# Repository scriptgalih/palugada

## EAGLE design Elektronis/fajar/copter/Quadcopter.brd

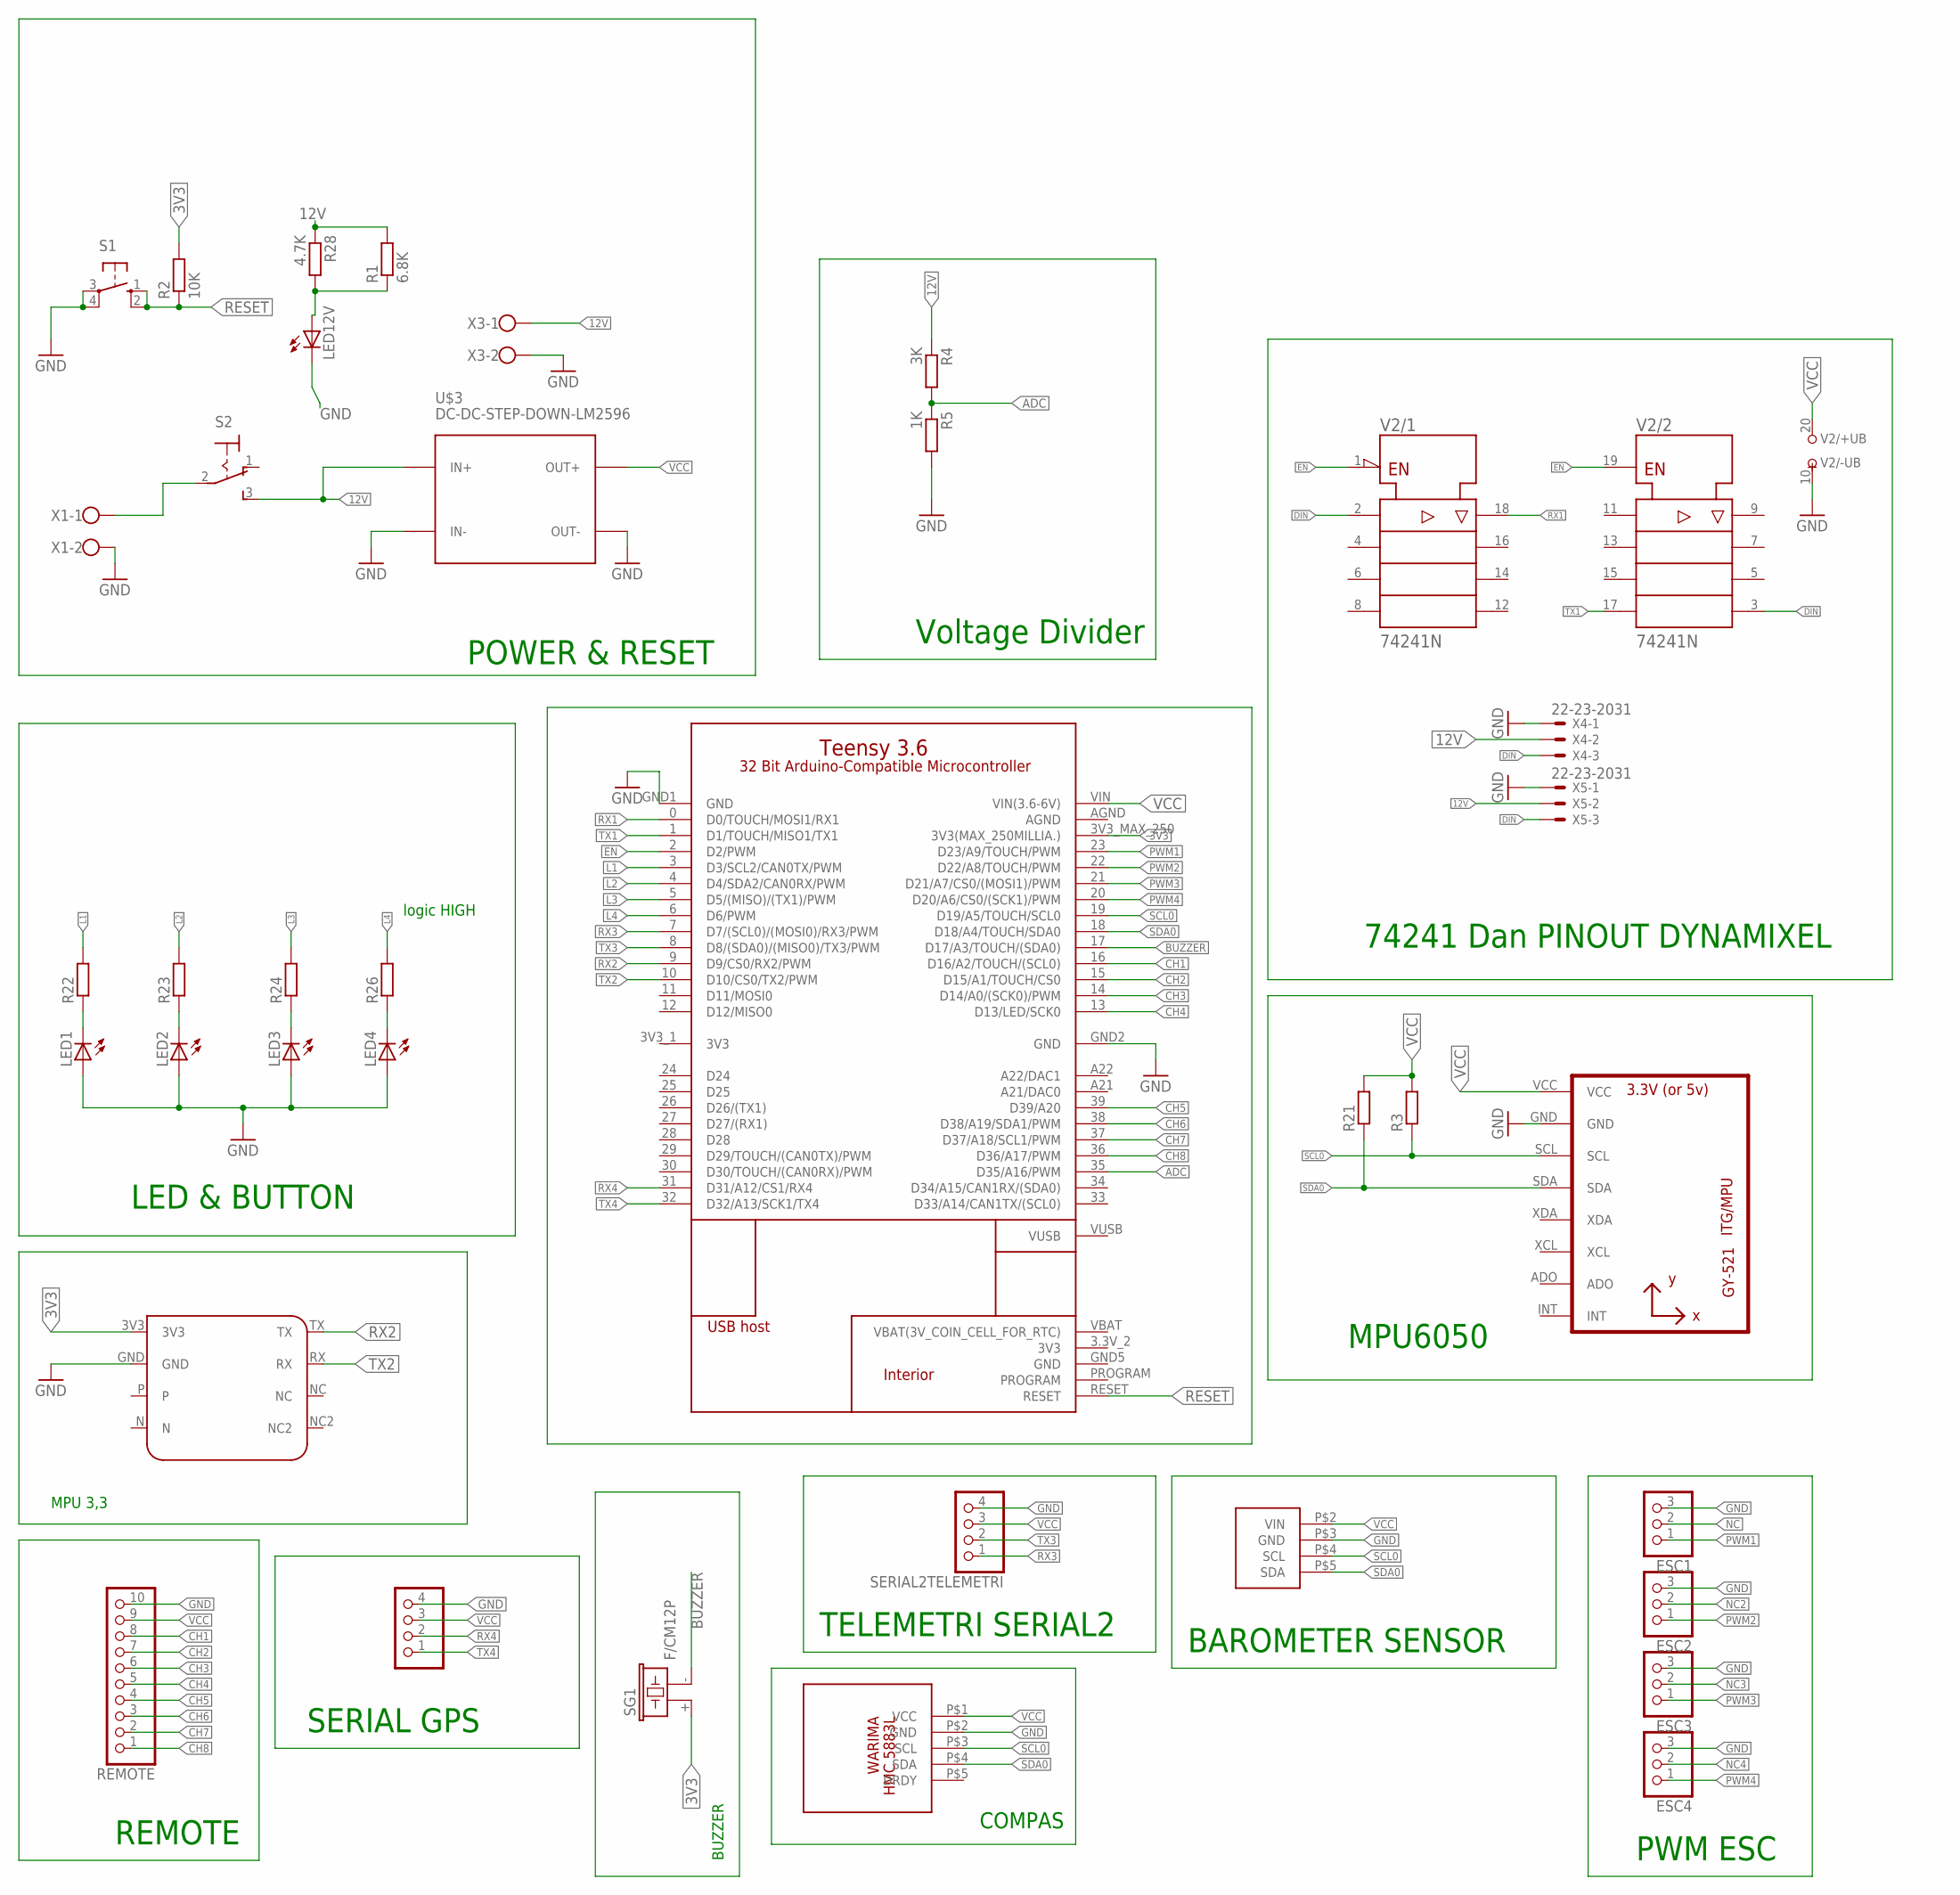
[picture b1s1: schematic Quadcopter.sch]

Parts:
ESC1, ESC2, ESC3, ESC4: PINHD-1X3; 1X03
LED1, LED2, LED3, LED4, LED12V: LED3MM
R1: 6.8K; 0207/10
R2: 10K; 0207/10
R3, R21, R22, R23, R24, R26: R-EU_0207/7; 0207/7
R4: 3K; 0207/10
R5: 1K; 0207/10
R28: 4.7K; 0207/10
REMOTE: PINHD-1X10; 1X10
S1: 10-XX; B3F-10XX
S2: 320-916
SERIAL2TELEMETRI, SERIAL2TELEMETRI1: PINHD-1X4; 1X04
SG1: F/CM12P
U1: GY-521MPU6050; GY-521
U$1: TEENSY-3.6_ONLY_HOLES
U$2: URANUS2
U$3: DC-DC-STEP-DOWN-LM2596
U$4: BMP180
U$5: HMC588L; HMC5883L
V2: 74241N; DIL20
X1, X3: W237-102
X4, X5: 22-23-2031

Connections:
3V3: R2.2, SG1.+ (1), U$1.3V3_1 (3V3), U$1.3V3_MAX_250 (3V3(MAX_250MILLIA.)), U$2.3V3
12V: R1.2, R4.1, R28.1, S2.3 (S), U$3.IN+, X3.1, X4.2, X5.2
ADC: R4.2, R5.1, U$1.35 (D35/A16/PWM)
AGND: U$1.AGND
BUZZER: SG1.- (2), U$1.17 (D17/A3/TOUCH/(SDA0))
CH1: REMOTE.8, U$1.16 (D16/A2/TOUCH/(SCL0))
CH2: REMOTE.7, U$1.15 (D15/A1/TOUCH/CS0)
CH3: REMOTE.6, U$1.14 (D14/A0/(SCK0)/PWM)
CH4: REMOTE.5, U$1.13 (D13/LED/SCK0)
CH5: REMOTE.4, U$1.39 (D39/A20)
CH6: REMOTE.3, U$1.38 (D38/A19/SDA1/PWM)
CH7: REMOTE.2, U$1.37 (D37/A18/SCL1/PWM)
CH8: REMOTE.1, U$1.36 (D36/A17/PWM)
DIN: V2.2 (A1), V2.3 (Y4), X4.3, X5.3
EN: U$1.2 (D2/PWM), V2.1 (!G), V2.19 (G)
GND: ESC1.3, ESC2.3, ESC3.3, ESC4.3, LED1.A, LED2.A, LED3.A, LED4.A, LED12V.K (C), R5.2, REMOTE.10, S1.3, S1.4 (P1), SERIAL2TELEMETRI.4, SERIAL2TELEMETRI1.4, U1.GND, U$1.GND1 (GND), U$1.GND2 (GND), U$2.GND, U$3.IN-, U$3.OUT-, U$4.P$3 (GND), U$5.P$2 (GND), V2.10 (-UB), X1.2, X3.2, X4.1, X5.1
L1: R22.2, U$1.3 (D3/SCL2/CAN0TX/PWM)
L2: R23.2, U$1.4 (D4/SDA2/CAN0RX/PWM)
L3: R24.2, U$1.5 (D5/(MISO)/(TX1)/PWM)
L4: R26.2, U$1.6 (D6/PWM)
unnamed: LED1.K (C), R22.1
unnamed: S2.2, X1.1
unnamed: LED2.K (C), R23.1
unnamed: LED3.K (C), R24.1
unnamed: LED4.K (C), R26.1
unnamed: LED12V.A, R1.1, R28.2
NC: ESC1.2
NC2: ESC2.2
NC3: ESC3.2
NC4: ESC4.2
PWM1: ESC1.1, U$1.23 (D23/A9/TOUCH/PWM)
PWM2: ESC2.1, U$1.22 (D22/A8/TOUCH/PWM)
PWM3: ESC3.1, U$1.21 (D21/A7/CS0/(MOSI1)/PWM)
PWM4: ESC4.1, U$1.20 (D20/A6/CS0/(SCK1)/PWM)
RESET: R2.1, S1.1 (S), S1.2 (S1), U$1.RESET
RX1: U$1.0 (D0/TOUCH/MOSI1/RX1), V2.18 (Y1)
RX2: U$1.9 (D9/CS0/RX2/PWM), U$2.TX
RX3: SERIAL2TELEMETRI.1, U$1.7 (D7/(SCL0)/(MOSI0)/RX3/PWM)
RX4: SERIAL2TELEMETRI1.2, U$1.31 (D31/A12/CS1/RX4)
SCL0: R3.1, U1.SCL, U$1.19 (D19/A5/TOUCH/SCL0), U$4.P$4 (SCL), U$5.P$3 (SCL)
SDA0: R21.1, U1.SDA, U$1.18 (D18/A4/TOUCH/SDA0), U$4.P$5 (SDA), U$5.P$4 (SDA)
TX1: U$1.1 (D1/TOUCH/MISO1/TX1), V2.17 (A4)
TX2: U$1.10 (D10/CS0/TX2/PWM), U$2.RX
TX3: SERIAL2TELEMETRI.2, U$1.8 (D8/(SDA0)/(MISO0)/TX3/PWM)
TX4: SERIAL2TELEMETRI1.1, U$1.32 (D32/A13/SCK1/TX4)
VCC: R3.2, R21.2, REMOTE.9, SERIAL2TELEMETRI.3, SERIAL2TELEMETRI1.3, U1.VCC, U$1.VIN (VIN(3.6-6V)), U$3.OUT+, U$4.P$2 (VIN), U$5.P$1 (VCC), V2.20 (+UB)

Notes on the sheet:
MPU 3,3
74241 Dan PINOUT DYNAMIXEL
MPU6050
BAROMETER SENSOR
LED & BUTTON
TELEMETRI SERIAL2
BUZZER
POWER & RESET
logic HIGH
SERIAL GPS
Voltage Divider
REMOTE
COMPAS
PWM ESC

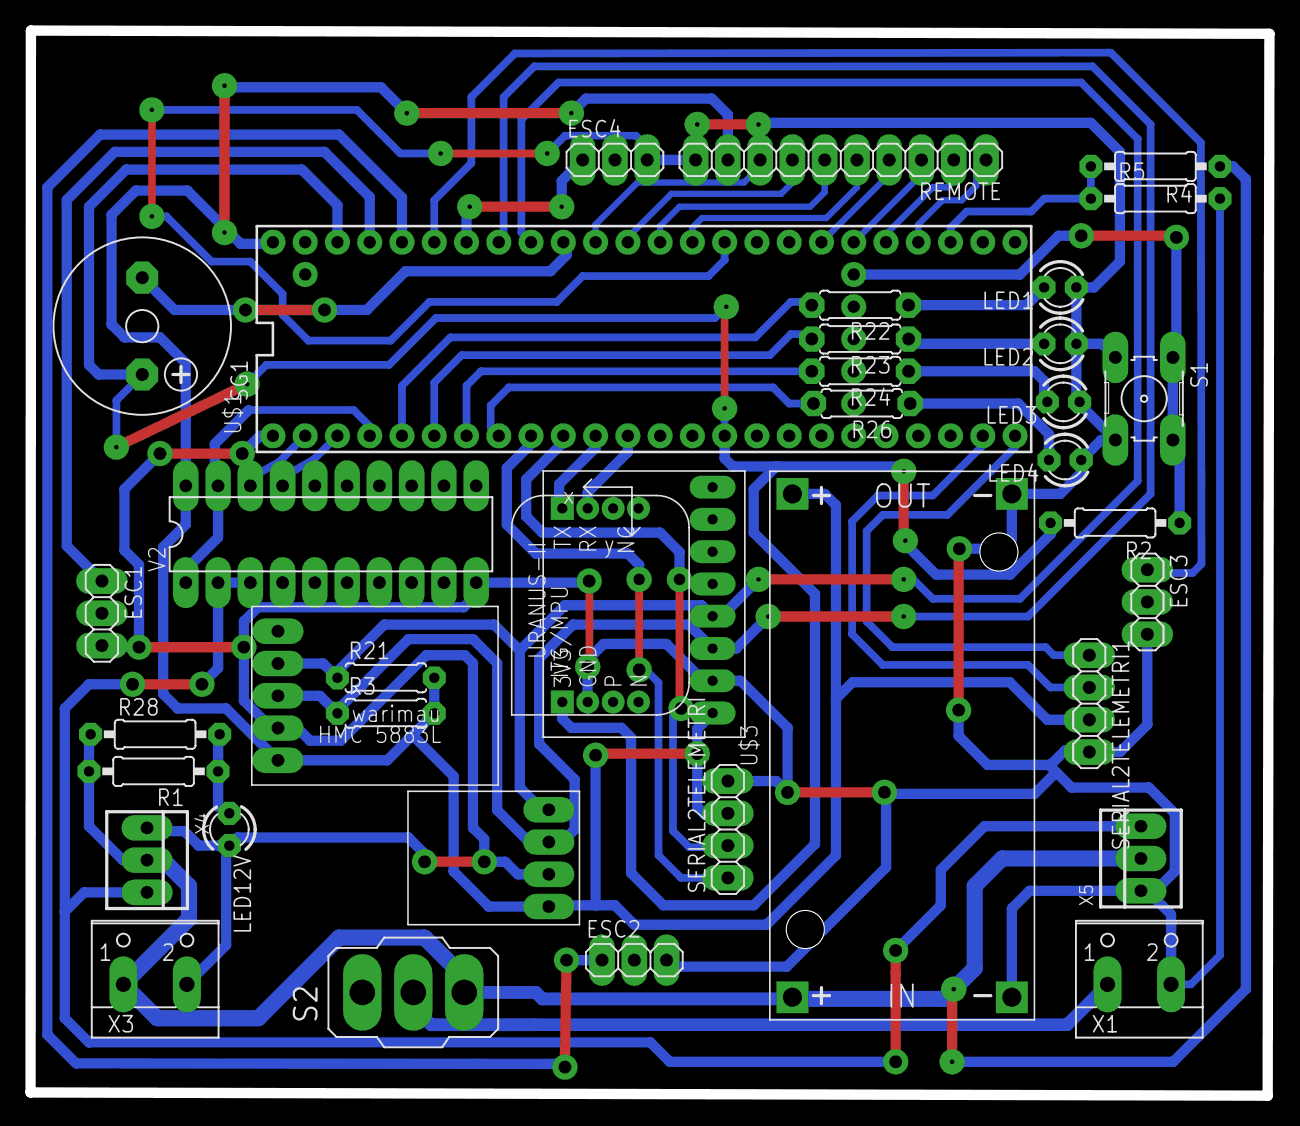
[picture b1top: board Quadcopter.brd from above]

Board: 2 copper layers, 97.5 x 83.8 mm, 37 parts (0 on the bottom side), 41 nets.

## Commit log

2020-01-20 define led
2020-01-20 define all pin
2020-01-20 ESC Calibrate
2020-01-20 Arming ESC
2020-01-20 add IMU URANUS, fix Arming safety, fix bug
2020-02-14 board 3 test esc
2020-03-16 board_fajar

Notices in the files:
parts and their libraries:
diy-modules: Released under the Creative Commons Attribution 4.0 International License: http://creativecommons.org/licenses/by/4.0
